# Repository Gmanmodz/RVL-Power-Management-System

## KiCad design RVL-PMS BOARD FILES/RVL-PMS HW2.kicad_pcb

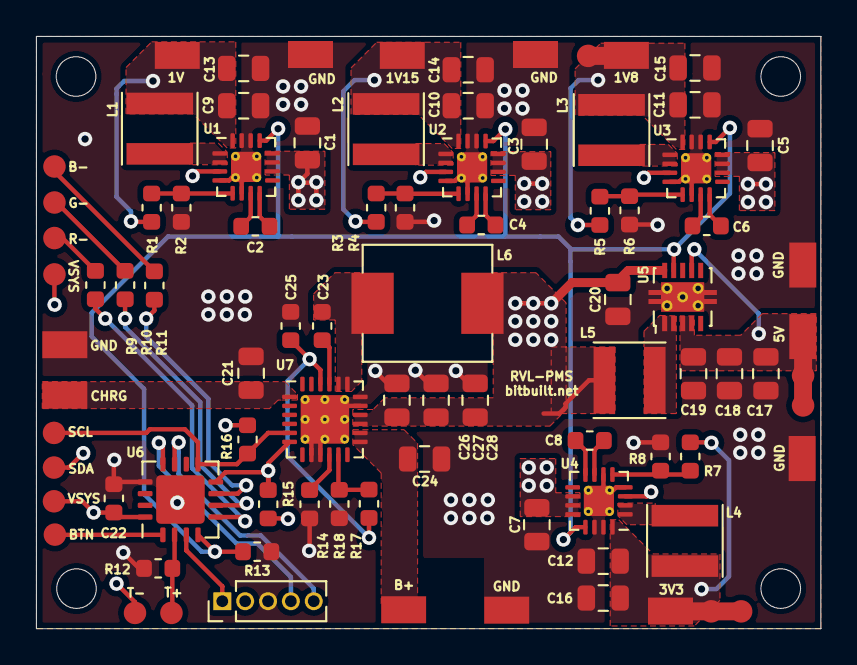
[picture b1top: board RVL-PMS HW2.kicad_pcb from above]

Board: 4 copper layers, 43.6 x 32.9 mm, 88 parts (0 on the bottom side), 45 nets.

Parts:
C1, C3, C5, C7, C9, C10, C11, C12, C13, C14, C15, C16, C17, C18, C19, C20, C21, C24, C26, C27, C28: C; C_0805_2012Metric
C2, C4, C6, C8, C22, C23, C25: C; C_0603_1608Metric
J1: Conn_01x05_Female; PinHeader_1x05_P1.27mm_Vertical
L1, L2, L3, L4, L5: L; L_Taiyo-Yuden_MD-4040
L6: L; ASPI-0630HI-2R2M-T15
R1, R2, R3, R4, R5, R6, R7, R8, R9, R10, R11, R12, R13, R14, R15, R16, R17, R18: R; R_0603_1608Metric
TP1, TP2, TP3, TP4, TP5, TP6, TP7, TP9, TP11, TP15, TP19, TP20, TP21: TestPoint; Voltage_pad
TP8, TP10, TP12, TP13, TP14, TP16, TP17, TP18, TP22, TP23, TP24, TP25, TP26, TP27, TP28: TestPoint; 1.25mm pad
U1, U2, U3, U4: TLV62095RGTx; VQFN-16-1EP_3x3mm_P0.5mm_EP1.68x1.68mm_ThermalVias
U5: Wii_reg-cache_Wii-reg-rescue_TPS61230-tps61230; VSON-10-1EP_3x3mm_P0.5mm_EP1.65x2.4mm_ThermalVias
U6: Wii_reg-cache_pic16f15324_PIC16F15324; QFN-16-1EP_4x4mm_P0.65mm_EP2.7x2.7mm
U7: BQ25895RTW; Texas_S-PWQFN-N24_EP2.7x2.7mm_ThermalVias

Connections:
3V3: C12.1, C16.2, L4.1, R7.2, TP4.1, TP24.1, TP25.1, U4.16
5V: C17.1, C18.1, C19.1, TP5.1, TP26.1, TP27.1, U5.3, U5.4, U5.7
AGND: C1.2, C3.2, C5.2, C7.2, C9.2, C10.2, C11.2, C12.2, C13.1, C14.1, C15.1, C16.1, C17.2, C18.2, C19.2, C20.1, C21.2, C22.1, C24.1, C25.1, C26.2, C27.2, C28.2, J1.3, R2.2, R4.2, R6.2, R8.2, R12.2, R13.2, R14.2, R18.1, TP6.1, TP7.1, TP9.1, TP11.1, TP20.1, TP21.1, U1.4, U1.6, U1.14, U1.15, U1.17, U2.4, U2.6, U2.14, U2.15, U2.17, U3.4, U3.6, U3.14, U3.15, U3.17, U4.4, U4.6, U4.14, U4.15, U4.17, U5.11, U6.13, U6.17, U7.8, U7.9, U7.17, U7.18, U7.25
B: R11.2, U6.7
EN: R13.1, U1.13, U2.13, U3.13, U4.13, U5.9, U6.4
G: R10.2, U6.6
MCLR: J1.1, U6.3
unnamed: C2.1, U1.7
unnamed: C2.2, U1.8
unnamed: C4.1, U2.7
unnamed: C4.2, U2.8
unnamed: C6.1, U3.7
unnamed: C6.2, U3.8
unnamed: C8.1, U4.7
unnamed: C8.2, U4.8
unnamed: C10.1, C14.2, L2.1, R3.2, TP2.1, U2.16
unnamed: C11.1, C15.2, L3.1, R5.2, TP3.1, TP28.1, U3.16
unnamed: C9.1, C13.2, L1.1, R1.2, TP1.1, U1.16
unnamed: C21.1, TP15.1, U7.1
unnamed: C23.1, U7.21
unnamed: C23.2, L6.2, U7.19, U7.20
unnamed: C24.2, TP19.1, U7.13, U7.14
unnamed: C25.2, R17.2, U7.22
unnamed: J1.4, U6.12
unnamed: J1.5, U6.11
unnamed: L1.2, U1.1, U1.2
unnamed: L2.2, U2.1, U2.2
unnamed: L3.2, U3.1, U3.2
unnamed: L4.2, U4.1, U4.2
unnamed: L5.2, U5.1, U5.2
unnamed: R1.1, R2.1, U1.5
unnamed: R3.1, R4.1, U2.5
unnamed: R5.1, R6.1, U3.5
unnamed: R7.1, R8.1, U4.5
unnamed: R9.1, TP8.1
unnamed: R10.1, TP10.1
unnamed: R11.1, TP12.1
unnamed: R14.1, U7.10
unnamed: R17.1, R18.2, U7.11
R: R9.2, U6.5
SCL: R16.1, TP18.1, U6.9, U7.5
SDA: R15.2, TP17.1, U6.8, U7.6
VSYS: C1.1, C3.1, C5.1, C7.1, C20.2, C22.2, C26.1, C27.1, C28.1, J1.2, L5.1, L6.1, R15.1, R16.2, TP16.1, TP22.1, TP23.1, U1.3, U1.10, U1.11, U1.12, U2.3, U2.10, U2.11, U2.12, U3.3, U3.10, U3.11, U3.12, U4.3, U4.10, U4.11, U4.12, U5.10, U6.16, U7.15, U7.16
VTEMP: R12.1, TP14.1, U6.2
btn: TP13.1, U6.1

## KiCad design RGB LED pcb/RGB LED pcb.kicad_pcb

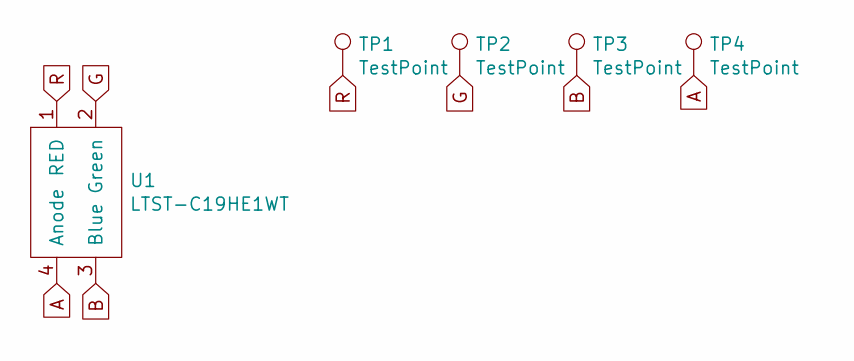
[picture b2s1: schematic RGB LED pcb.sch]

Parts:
TP1, TP2, TP3, TP4: TestPoint; 1.25mm pad
U1: LTST-C19HE1WT

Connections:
A: TP4.1, U1.4 (Anode)
B: TP3.1, U1.3 (Blue)
G: TP2.1, U1.2 (Green)
R: TP1.1, U1.1 (RED)

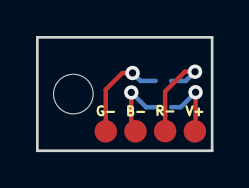
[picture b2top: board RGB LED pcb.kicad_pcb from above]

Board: 2 copper layers, 9.7 x 6.3 mm, 5 parts (1 on the bottom side), 4 nets.

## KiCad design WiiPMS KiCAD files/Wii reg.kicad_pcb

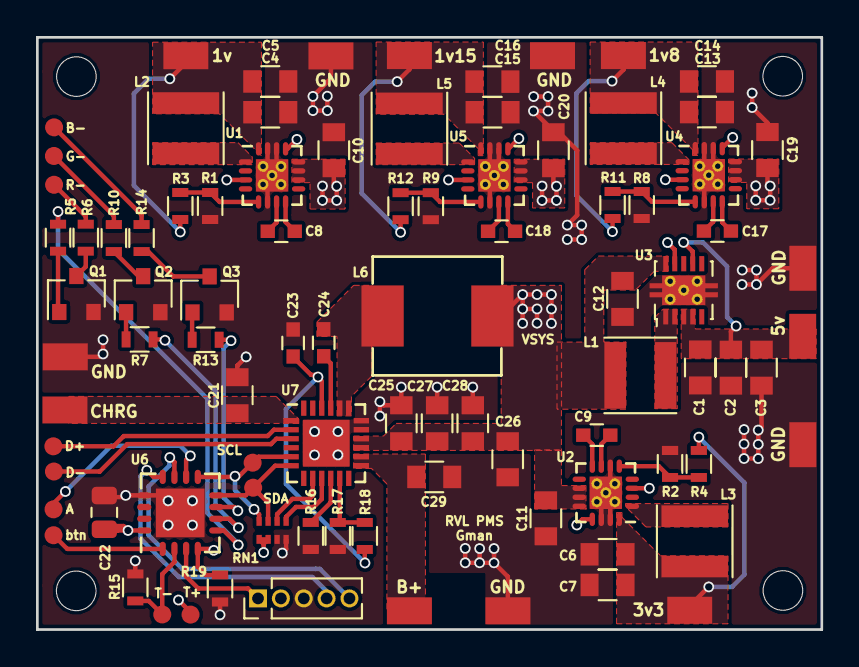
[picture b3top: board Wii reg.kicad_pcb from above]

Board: 4 copper layers, 43.6 x 32.9 mm, 91 parts (0 on the bottom side), 56 nets.

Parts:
1v, 1v8, 1v15, 3v3, 5v: TEST_1P; TP2
B+: TEST_1P; TP2
C1, C2, C3, C4, C5, C6, C7, C10, C11, C12, C13, C14, C15, C16, C19, C20, C21, C25, C26, C27, C28, C29: C; C_0805
C8, C9, C17, C18, C23, C24: C; C_0603
C22: C; C_0805_2012Metric
CHRG: TEST_1P; TP2
GND: TEST_1P; TP2
GND#2, GND#3, GND#4, GND#5, GND#6: TEST_1P; TP2
J4, J5, J8, J11, J12, J14, J16, J17, J18, J24, J26: TEST_1P; TP1
J25: Conn_01x05; Pin_Header_Straight_1x05_Pitch1.27mm
L1, L2, L3, L4, L5: L; L_Taiyo-Yuden_MD-4040
L6: L; ASPI-0630HI-2R2M-T15
Q1, Q2, Q3: 2N3904; SOT-23_custom
R1, R2, R3, R4, R5, R6, R7, R8, R9, R10, R11, R12, R13, R14, R15, R16, R17, R18, R19: R; R_0603
RN1: R_Pack04; RA_0804
U1, U2, U4, U5: tlv62095; QFN-16-1EP_3x3mm_Pitch0.5mm_ThermalVias
U3: TPS61230; VSON-10-1EP_3x3mm_Pitch0.5mm_ThermalPad
U6: PIC16F15324; UQFN-16-1EP_4x4mm_Pitch0.65mm
U7: bq25895m; QFN-24-1EP_4x4mm_Pitch0.5mm
wREF**: MountingHole_2.2mm_M2

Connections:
1v: 1v.1, C4.1, C5.1, L2.1, R3.2, U1.16
1v8: 1v8.1, C13.1, C14.1, L4.1, R11.2, U4.16
1v15: 1v15.1, C15.1, C16.1, L5.1, R12.2, U5.16
3v3: 3v3.1, C6.1, C7.1, L3.1, R4.2, U2.16
5v: 5v.1, C1.1, C2.1, C3.1, U3.3, U3.4, U3.7
BLUE: R13.2, U6.7
CE: RN1.8, U7.9
EN: R19.1, U1.13, U2.13, U3.9, U4.13, U5.13, U6.4
GND: C1.2, C2.2, C3.2, C4.2, C5.2, C6.2, C7.2, C10.1, C11.1, C12.1, C13.2, C14.2, C15.2, C16.2, C19.1, C20.1, C21.1, C22.1, C23.1, C25.2, C26.1, C27.2, C28.2, C29.2, GND.1, GND#2.1, GND#3.1, GND#4.1, GND#5.1, GND#6.1, J25.3, Q1.1, Q2.1, Q3.1, R1.2, R2.2, R8.2, R9.2, R15.2, R16.2, R17.1, R19.2, RN1.1, RN1.2, U1.6, U1.14, U1.15, U1.17, U2.6, U2.14, U2.15, U2.17, U3.11, U4.6, U4.14, U4.15, U4.17, U5.6, U5.14, U5.15, U5.17, U6.13, U6.17, U7.17, U7.18, U7.25
GREEN: R7.1, U6.6
MCLR: J25.1, U6.3
unnamed: C8.1, U1.8
unnamed: C8.2, U1.7
unnamed: C9.1, U2.8
unnamed: C9.2, U2.7
unnamed: C17.1, U4.8
unnamed: C17.2, U4.7
unnamed: C18.1, U5.8
unnamed: C18.2, U5.7
unnamed: C21.2, CHRG.1, U7.1
unnamed: C24.1, L6.2, U7.19, U7.20
unnamed: C24.2, U7.21
unnamed: B+.1, C29.1, U7.13, U7.14
unnamed: J4.1, R6.1
unnamed: J5.1, R10.1
unnamed: J8.1, R14.1
unnamed: J17.1, U7.2
unnamed: J18.1, U7.3
unnamed: J24.1, U6.10
unnamed: J25.4, U6.12
unnamed: J25.5, U6.11
unnamed: L1.2, U3.1, U3.2
unnamed: L2.2, U1.1, U1.2
unnamed: L3.2, U2.1, U2.2
unnamed: L4.2, U4.1, U4.2
unnamed: L5.2, U5.1, U5.2
unnamed: Q1.2, R5.2
unnamed: Q1.3, R6.2
unnamed: Q2.2, R7.2
unnamed: Q2.3, R10.2
unnamed: Q3.2, R13.1
unnamed: Q3.3, R14.2
unnamed: R1.1, R3.1, U1.5
unnamed: R2.1, R4.1, U2.5
unnamed: R8.1, R11.1, U4.5
unnamed: R9.1, R12.1, U5.5
unnamed: R16.1, U7.10
unnamed: R17.2, R18.2, U7.11
OTG: RN1.7, U7.8
RED: R5.1, U6.5
REGN: C23.2, R18.1, U7.22
SCL: J14.1, RN1.5, U6.9, U7.5
SDA: J16.1, RN1.6, U6.8, U7.6
VSYS: C10.2, C11.2, C12.2, C19.2, C20.2, C22.2, C25.1, C26.2, C27.1, C28.1, J12.1, J25.2, L1.1, L6.1, RN1.3, RN1.4, U1.3, U1.10, U1.11, U1.12, U2.3, U2.10, U2.11, U2.12, U3.10, U4.3, U4.10, U4.11, U4.12, U5.3, U5.10, U5.11, U5.12, U6.16, U7.15, U7.16
Vtemp: J11.1, R15.1, U6.2
button: J26.1, U6.1

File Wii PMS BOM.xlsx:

Wii Power Management System | Total: | 29.946
Reference | Description | Price | Manufacturer P/N | Vender | Link
U1, U2, U4, U5 | IC REG BUCK ADJ 4A SYNC 16QFN | 7.48 | TLV62095RGTR | Digikey | https://www.digikey.com/product-detail/en/texas-instruments/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
U3 | TPS61232DRCR | 2.54 | TPS61232DRCR | Digikey | https://www.digikey.com/product-detail/en/texas-instruments/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
U6 | IC MCU 8BIT 7KB FLASH 16UQFN | 0.85 | PIC16F15324T-I/JQ | Digikey | https://www.digikey.com/product-detail/en/microchip-technolo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
U7 | BQ25895M | 3.36 | BQ25895MRTWR | Digikey | https://www.digikey.com/products/en?keywords=296-42447-1-ND%09
R1, R2, R8, R9 | RES SMD 160K OHM 1% 1/10W 0603 | 0.4 | RC0603FR-07160KL | Digikey | https://www.digikey.com/product-detail/en/yageo/RC0603FR-071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
R3 | RES SMD 44.2K OHM 1% 1/10W 0603 | 0.1 | RES SMD 160K OHM 1% 1/10W 0603 | Digikey | https://www.digikey.com/product-detail/en/yageo/RC0603FR-074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
R4 | RES SMD 510K OHM 1% 1/10W 0603 | 0.1 | RC0603FR-07510KL | Digikey | https://www.digikey.com/product-detail/en/yageo/RC0603FR-075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
R5, R7, R13, R15, R17, R18, R19 | RES SMD 10K OHM 1% 1/10W 0603 | 0.7 | RC0603FR-0710KL | Digikey | https://www.digikey.com/product-detail/en/yageo/RC0603FR-071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
R6, R10, R14 | RES 100 OHM 1% 1/10W 0603 | 0.3 | RMCF0603FT100R | Digikey | https://www.digikey.com/product-detail/en/stackpole-electron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
R11 | RES SMD 200K OHM 1% 1/10W 0603 | 0.1 | RC0603FR-07200KL | Digikey | https://www.digikey.com/product-detail/en/yageo/RC0603FR-072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
R12 | RES SMD 75K OHM 1% 1/10W 0603 | 0.1 | RC0603FR-0775KL | Digikey | https://www.digikey.com/product-detail/en/yageo/RC0603FR-077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
R16 | RES SMD 261 OHM 1% 1/10W 0603 | 0.1 | RC0603FR-07261RL | Digikey | https://www.digikey.com/product-detail/en/yageo/RC0603FR-072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
RN1 | RES ARRAY 4 RES 10K OHM 0804 | 0.1 | EXB-28V103JX | Digikey | https://www.digikey.com/product-detail/en/panasonic-electron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
C1, C2, C3, C4, C5, C6, C7, C10, C11, C12, C13, C14, C15, C16, C19, C20 | CAP CER 22UF 6.3V X5R 0805 | 2.336 | CL21A226MQQNNNE | Digikey | https://www.digikey.com/product-detail/en/samsung-electro-me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
C8, C9, C17, C18 | CAP CER 10000PF 50V X7R 0603 | 0.4 | 06035C103KAT4A | Digikey | https://www.digikey.com/product-detail/en/avx-corporation/06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
C21, C22 | CAP CER 1UF 25V X7R 0805 | 0.76 | GCM21BR71E105KA56L | Digikey | https://www.digikey.com/product-detail/en/murata-electronics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
C23 | CAP CER 4.7UF 16V X5R 0603 | 0.29 | CL10A475KO8NNNC | Digikey | https://www.digikey.com/product-detail/en/samsung-electro-me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
C24 | CAP CER 0.047UF 25V X7R 0603 | 0.13 | C0603C473K3RACTU | Digikey | https://www.digikey.com/product-detail/en/kemet/C0603C473K3R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
C25, C26, C27, C29 | CAP CER 10UF 16V X5R 0805 | 0.68 | CL21A106KOQNNNG | Digikey | https://www.digikey.com/product-detail/en/samsung-electro-me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
L1, L2, L3, L4, L5 | FIXED IND 1UH 5.1A 27 MOHM SMD | 3.6 | MDWK4040T1R0MM | Digikey | https://www.digikey.com/product-detail/en/taiyo-yuden/MDWK40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
L6 | FIXED IND 2.2UH 8A 20 MOHM SMD | 0.89 | ASPI-0630HI-2R2M-T15 | Digikey | https://www.digikey.com/product-detail/en/abracon-llc/ASPI-0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
Q1, Q2, Q3 | TRANS NPN 40V 0.2A SOT23 | 0.3 | MMBT3904-TP | Digikey | https://www.digikey.com/product-detail/en/micro-commercial-c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
TH1 | THERMISTOR NTC 10KOHM 3988K BEAD | 3.72 | B57861S0103A043 | Digikey | https://www.digikey.com/product-detail/en/epcos-tdk/B57861S0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
RGB led | LED RGB DIFFUSED CHIP SMD | 0.61 | LTST-C19HE1WT | Digikey | https://www.digikey.com/products/en?keywords=160-2162-1

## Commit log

2019-03-16 first
2019-03-18 Update Wii PMS BOM.xlsx
    Fixed row 9 part#
2019-03-21 update 1
    changed some mode logic. Made a distinction between low battery and charging.
2019-05-22 Set TREG
2019-10-02 WiiPMS firmware v2
    Rewrote the project to use new features including powered off charging indicator and using jeff's dynamic pd source negotation library.
2019-10-26 Corrected VREG config
2020-04-27 Added STUSB DEVICE_ID_B for compatibility with USBCBoard
2020-10-14 Updated new board files and code
    This new code is not to be used on the older PMS boards. I deleted the transistor LED drivers because they weren't needed and the code now has inverted the LED outputs.
2020-10-21 Compiled without nvmflash
2020-11-28 fixed mistake in chrg_timer variable
